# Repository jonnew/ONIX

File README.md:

# NOTE: This repository has been split into individual `onix-<project>` repos that are hosted on the [open-ephys github account](https://github.com/open-ephys). This repo has been archived.

[ONIX](https://open-ephys.github.io/onix-docs/index.html) is a collection
of [ONI](https://github.com/jonnew/ONI)-compatible hardware and API
for serialized, very-high channel count, closed-loop electrophysiology. It is
an evolution of the first-generation hardware and software introduced in [Open
Ephys project](http://www.open-ephys.org/) and involves many of the same
developers.  The firmware and API are general purpose -- they can be used to
acquire from and control custom headstages with arbitrary arrangements of
sensors and actuators (e.g. cameras, bioamplifier chips, LED drivers, etc.) and
are not limited to the hardware in this repository.

__Documentation__ : https://open-ephys.github.io/onix-docs/index.html

__Citing this work__: 

1. Citing the paper

  - TODO

2. Citing the repository itself

  - 

## Features
- Follows the [ONI](https://github.com/jonnew/ONI)-specification for serialization protocols, host communication
  protocols, device drivers, and host API
- Firmware and API permit acquisition and control of arbitrary arrangements of
  sensors and actuators:

    - Headstages
    - Miniscopes
    - Photometry systems
    - Etc.

- Submillisecond round-trip communication from brain, through host PC's main
  memory, and back again.
- Headstages:

    - 64-, 128-, 256-channels of electrophysiology
    - Optogenetic stimulation
    - Electrical stimulation
    - 3D-pose measurement
    - Data, user control, and power via a tiny coaxial cable
    - Wireless communication

- Low-level API implementation
- High-level API language bindings and existing integration with [Open Ephys
  GUI](http://www.open-ephys.org/gui/) and [Bonsai](http://bonsai-rx.org/).
- Quality documentation and easy routes to purchasing assembled devices.

## Software

1. API: https://github.com/jonnew/liboni
2. Bonsai package: coming soon
3. Open Ephys GUI plugin: coming soon

## Hardware

### [eib-64](eib-64/README.md)
64 Channel electrode interface board. Designed for small rodent tetrode
electrophysiology. Works with [headstage-64](./headstage-64/README.md).

### [eib-128](eib-128/README.md)
128 Channel electrode interface board. Designed for large rodent tetrode
electrophysiology. Works with [headstage-256](./headstage-256/README.md).

### [eib-256](eib-256/README.md)
256 Channel electrode interface board. Designed for large rodent tetrode
electrophysiology. Works with [headstage-256](./headstage-256/README.md).

### [headstage-64](headstage-64/README.md)
Serialized, multifunction headstage for small rodents. Supports 64 channels.
Designed to interface with [eib-64](./eib-64/README.md).

### [headstage-256](headstage-256/README.md)
Serialized, multifunction headstage for large rodents. Supports both 128 or 256
channels. Designed to interface with [eib-128](./eib-128/README.md) or
[eib-256](./eib-256/README.md)

### [fmc-host](fmc-host/README.md)
Base board for facilitating PCIe communication, via FMC compatiable and
PCIe-capable FPGA based board (e.g. [Numato Lab
Nereid](https://numato.com/product/nereid-kintex-7-pci-express-fpga-development-board).
This board plugs into the FMC connector on the base board. It provides
communication with one headstage and lots of other analog and digital IO.

### [analog-io-breakout](analog-io-breakout/README.md)
Passive breakout board for acquiring and generating analog signals through BNC,
SMA, ribbon, or straight wire connections. Plugs into fmc-host using a 26-pin
shrunk delta ribbon cable.

### [nanoz-adapter-64](./nanoz-adapter-64/README.md)
Adapter to interface eib-64 with the popular
[nanoZ](http://www.white-matter.com/nanoz/) electrode impedance tester and
plating device.

### [nanoz-adapter-128-256](./nanoz-adapter-128-256/README.md)
Multiplexed adapter to interface eib-128 and eib-256 with the popular
[nanoZ](http://www.white-matter.com/nanoz/) electrode impedance tester and
plating device.

### [test-board-64](./test-board-64)
Test board for headstage-64. Allows injecting simulated biopotentials into
headstage modules via a selectable passive attenuator. Provides LEDs and
simulated electrical loads for optical and electrical stimulation.

### [test-board-128-256](./test-board-128-256)
Test board for headstage, and headstage-256 modules. Allows injecting simulated
biopotentials into headstage modules via a selectable passive attenuator.
Provides LEDs and simulated electrical loads for optical and electrical
stimulation.

### [headstage-programmer](headstage-programmer/README.md)
JTAG breakout for the [Intel USB Blaster 2](https://www.digikey.com/short/qqw7hm)
used to program the headstages' MAX10 FPGA.

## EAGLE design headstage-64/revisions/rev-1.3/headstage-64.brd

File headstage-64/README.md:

:warning: This project has moved to a dedicated repository: https://github.com/open-ephys/onix-headstage-64
This folder should be considered archived.

# headstage-64
Serialized, multifunction headstage for small rodents. Designed to function
with [eib-64](../eib-64/README.md).

## Electrophysiology
This heastage uses an [Intan RHD2164]() bioamplifier chip. This chip provides:
- 64 channels of ephys are pinned out through the large mezzanine connector on the
  bottom of the headstage
- 3 auxiliary channels
    - AUX 1 and 2 are pinned out on the bottom of the headstage to an unpopulated
      mezzanine connector
    - Channel 3 is tied to the electrical stimulator's current measurement circuit

## 3D Position Tracking
Headstage-64 featurs 4 TS4231 Vive lighthouse receivers for 3D position
tracking. They work with V2 lighthouses. To set up tracking,

1. Serial into each of the basestations using the USB connection on the back
   and set up a terminal conneciton using `screen /dev/ttyACM0 115200` or
   similar

2. Once connected you can hit Tab to see commands

3. Set the mode of one base staiton to 1 (mode 1) and the other to 2 (mode 2).

## 3D Orientation Tracking
TODO

## Neural Stimulators
Headstage-64 provides onboard electrical and optical stimulation. Stimulus
trains can be parameterized in a similar way to the master-8 or pulse pal.
Electical and optical stimulus trains cannot be delivered simultaneously.
If there is a conflict, electical stimuluation will take priority and optical
stimulus triggers will be ignored.

To acheive the shortest latency, electrical and optical stimulation can be triggered
using the GPIO1 serializer output. Because both stimulators share this trigger line,
it is important to only enable one of the devices (using its ENABLE register) prioir
to toggling this pin.

### Optical Stimulation

Q. Can i parallel the Cathode connections to increase max current
A. Yes.

### Electical Stimulation
The electrical stimulation cicuit is an improved Howland current pump followed by
an precision current measurement circuit. The current pump is supplied by +/-15V
rails and can supply up to +/- 2.5 mA. The output c

ISTIM = (VDAC  - 2.5)/1000.
e.g.
VDAC = 2.5   -> ISTIM = 0
VDAC = 5.0   -> ISTIM = 2.5 mA
VDAC = 0.0   -> ISTIM = -2.5mA

and

Imeas = 400 * ISTIM + 1.25V
e.g.
ISTIM = 0      -> IMEAS = 1.25V
ISTIM = 2.5mA  -> IMEAS = 2.25V
ISTIM = -2.5mA -> IMEAS = 0.25V

## Schematic

## Gerber Files
{% include gerber_layers.md %}

## Bill of Materials
The BOM is located on [this google
sheet](https://docs.google.com/spreadsheets/d/1F-KWcdvH_63iXjZf0cgCfDiFX6XXW3qw6rlR8DZrFpQ/edit#gid=138167638).

## FPGA Pinout
The FPGA pinout is located on [this google
sheet](https://docs.google.com/spreadsheets/d/1oJoQ89dJNL9LIiTrRnwJ_9KGiLzJ53Tju5Lfchuvsb0/edit#gid=2100166621).

## Connector Pinout
The headstage connector pinout (ADC input mapping, stimulation connections,
etc) is located on [this google
sheet](https://docs.google.com/spreadsheets/d/11wRDYOqHN5lPb03yUdfXfK0zvaDYsVetplaNK-R90Gg/edit#gid=663991061)

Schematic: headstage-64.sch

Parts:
C1: 0.1uF; 0201T; PARTNP CL03A104KA3NNNC
C2, C3, C5, C6, C18, C27, C32, C33, C35: 0.1uF; 0201T; PARTNO C0603X5R1C104K030BC
C4, C8, C9: 0.1uF; 0201T; PARTNO CL03A104KA3NNNC
C7: 4.7uF; 0402T; PARTNO CL05A475MO5NUNC
C10, C14, C15, C21, C22, C45, C51, C59, C66, C71: 10nF; 0201T
C11, C13, C16, C20, C23, C30, C31, C48: 0.1uF; 0201T
C12, C17: 4.7uF; 0402T; PARTNO GRM155R61A475MEAAD
C19, C28, C34, C36, C49: 1uF; 0201T; PARTNO CL03A105MP3ZSNH
C24: 22uF; 0402T; PARTNO CL05A226MQ5QUNC
C25: 0.1uF; 0201T; PARTNO C1005X7R1H104K050BB
C26: 47nF; 0201T; PARTNO C1005X7R1H473K050BB
C29: 10nF; 0201T; PARTNO GRM033R71E103KE14D
C37, C39, C41, C55, C69: 10uF; 0402T; PARTNO CL05A105KO5NNNC
C38, C40, C54, C56: 10uF; 0402T; PARTNO CL05A106MQ5NUNC
C42, C64: 0.22uF; 0402T; PARTNO UMK105BJ224KV-F
C43: 2.2nF; 0201T
C44, C50, C58, C65: 4.7nF; 0201T
C46, C52, C60, C67: 22nF; 0201T
C47, C61: 47nF; 0201T
C53, C62, C68: 0.47uF; 0201T; PARTNO GRM033R60J474KE90D
C57: 10pF; 0201T
C63, C72: 1uF; 0402T; PARTNO CL05A105KO5NNNC
C70: 4.7uF; 0402T; PARTNO CL05A105KO5NNNC
C73: 22uF; 0402T; PARTNO CL05A226MQ6ZUN8
D1, D2, D3: SESD0402X1UN-0020-090; 0402T-DFN
D4, D5, D6, D8: VEMD1160X01; 0805PT
D7: XZVGR155W; LED-0201T
D9: VSKY05401006; CLP1006-2L
J1, J3, J6: COAX_XFL; X_FL_R_SMT_1(02)
J2, J4, J7: PINHD-1X4HEADSTAGE64-DAUGHTER-CARD-CASTELLATED; HEADSTAGE64-DAUGHER-CARD-CASTELLATED
J5: PINHD-1X4HEADSTAGE64_DAUGHTER-CARD; HEADSTAGE-64-DAUGHTER-CARD
J8: DF40C-70DP-0.4V(51); DF40-70HEAD-LESS-SILK
J9: PINHD-1X5_HALF_CONNETOR; DF40-10HEAD_HALF
L1, L3, L5: CIG21L4R7MNE; 0805T
L2: BLM18KG601SN1D; 0603T
L4: CBC3225T101MR; 1210T
L6, L7, L8, L10: BLM15PX601SN1D; 0402T; PARTNO BLM15PX601SN1D
L9, L11: MLZ2012M100WT000; 0805T
L12: LQM21PN1R0NGRD; 0805T
R1: 9k, 0.1%; 0201T
R2: 1k, 0.1%; 0201T
R3, R9, R10, R20, R21, R43: 1k; 0201T
R4, R5, R6, R7, R8, R11, R14, R16, R17, R18, R19: 10k, 0.1%; 0201T
R12, R31, R34, R35, R47: 100; 0201T
R13: 2.86k; 0201T
R15: 590; 0201T
R22, R23, R27, R28, R32, R33, R38, R39, R40, R49, R53, R54, R55, R56, R57: 10k; 0201T
R24, R26, R36, R42: 15k; 0201T
R25: 49.9; 0201T
R29: 0; 0201T
R30: 100k; 0201T
R37: 2k; 0201T
R41, R44, R51, R52: 4.7k; 0201T
R45, R50: 1M; 0201T
R46: 90.9k; 0201T
R48: 83.3k; 0201T
TP1, TP2, TP5, TP6: VCC; TP07R
TP3, TP4: TPTP09R; TP09R
TP7, TP8, TP9, TP10, TP11, TP12, TP13: TPTP06R; TP06R
TP14: gnd; TP06R
TP15: VCC; TP06R
U1: ADA4062-4ACPZ-R7; CP_16_27-L
U2: AD5681RBCPZ-1RL7; CP_8_10-L
U3: CAT4016_QFN; QFN24-4X4; PARTNO CAT4016HV6-GT2
U4: TPL0501_UQFN; UQFN; PARTNO TPL0501-100RSER
U5: DG509B; MQFN16-1.8X2.6
U6, U8, U11, U12: TS4231; WLCSP3X3
U7: RHD2064_BGA; BGA104_0.5MM
U9: DS90UB913A_WQFN; WQFN32-5X5
U10: BNO055; LGA-28-3.8X5.2
U13, U15: TLV70733; X2SON
U14: 10M08DC; VBGA81-4X4
U16: LT3463; DFN103X3
U17: TLV70725; X2SON
U18: TPS62621; XBGA6_1.2X0.8
U19: ASCO-50.000MHZ-EK-T3; ASCO
U20: TLV70712; X2SON

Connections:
!IMU_BL: R28.2, U10.4 (!BOOT_LOAD)
!IMU_RESET: R32.1, U10.11 (!RESET)
$N324: C50.1, C51.1, C52.1, C53.1, C54.1, L10.2, U14.A8 (VCCD_PLL2)
+1V2: C43.1, C44.1, C45.1, C46.1, C47.1, C48.1, C49.1, C73.1, L10.1, U14.B2 (VCC), U14.B9 (VCC), U14.H2 (VCC), U14.H8 (VCC), U20.1 (OUT)
+1V8: C13.1, C14.1, C15.1, C16.1, C17.1, C70.1, L6.1, L8.1, L12.1, R27.1, U9.11 (VDDT), U9.28 (VDDD), U18.C1 (FB)
+2V5: C56.1, C65.1, C66.1, C67.1, C68.1, C72.1, U14.B1 (VCCA3), U14.B8 (VCCA2), U14.J1 (VCCA1), U14.J9 (VCCA4), U17.1 (OUT), U20.3 (EN), U20.4 (IN)
+3V3: C3.1, C5.1, C18.1, C20.1, C21.1, C27.1, C31.1, C32.1, C35.1, C40.1, C58.1, C59.1, C60.1, C61.1, C62.1, C71.1, R22.1, R28.1, R32.2, R33.1, R37.1, R38.1, R39.1, R40.1, R41.2, R44.1, R51.2, R52.1, R53.1, R54.1, R55.1, R56.1, TP14.TP, U2.2 (VLOGIC), U4.7 (VDD), U6.C3 (DVDD), U8.C3 (DVDD), U9.25 (VDDIO), U10.3 (VDD), U10.28 (VDDIO), U11.C3 (DVDD), U12.C3 (DVDD), U14.D5 (VCCIO8), U14.E4 (VCCIO1_2), U14.E6 (VCCIO5_6), U14.F5 (VCCIO3), U15.1 (OUT), U19.1 (EN), U19.4 (VCC)
+3V3_AN: C30.2, C38.1, J9.4 (5), U7.M15 (VDD), U7.M16 (LVDS_EN), U7.N2 (VDD), U7.N15 (VDD), U13.1 (OUT)
+15V0: C1.1, C8.1, C42.1, R45.2, U1.3 (V+), U5.12 (V+), U16.1 (VOUT1)
-15V0: C4.1, C9.1, C57.2, C64.1, D9.A, R50.1, U1.10 (V-), U1.PAD (V-), U5.1 (V-)
AGND: C29.2, C30.1, C37.2, C38.2, J8.70, J8.M1, J8.M2, J8.M4, J9.M1 (1), J9.M2 (6), L7.2, R29.1, TP1.TP, U7.M2 (VESD), U7.M17 (GND), U7.N1 (GND), U7.N6 (GND), U13.2 (GND), U13.PAD (GND)
AUXIN2: J9.2 (3), TP6.TP, U7.N4 (AUXIN2)
AUXIN3: J9.1 (2), TP5.TP, U7.N3 (AUXIN1)
CONFIG_SEL: R57.1, U14.C6 (CONFIG_SEL/C6)
CONF_DONE: R56.2, U14.A2 (DIFFIO_RX_T24N/CONF_DONE/A2)
DAC_CS: U2.5 (!SYNC), U14.A5 (DIFFIO_RX_T18N/A5)
DATA1: U6.C1 (D/CFGDATA), U14.C7 (DIFFIO_RX_R33P/PLL_R_CLKOUTP/C7)
DATA2: U8.C1 (D/CFGDATA), U14.C3 (DIFFIO_RX_T26N/C3)
DATA3: U11.C1 (D/CFGDATA), U14.A7 (DIFFIO_RX_T16P/A7)
DATA4: U12.C1 (D/CFGDATA), U14.B6 (DIFFIO_RX_T16N/DEV_CLRN/B6)
DIN0: U9.19 (DIN0), U14.J6 (DIFFIO_TX_RX_B12P/J6)
DIN1: U9.20 (DIN1), U14.G6 (DIFFIO_TX_RX_B14N/G6)
DIN2: U9.21 (DIN2), U14.H7 (DIFFIO_TX_RX_B14P/H7)
DIN3: U9.22 (DIN3), U14.J7 (DIFFIO_TX_RX_B16N/J7)
DIN4: U9.23 (DIN4), U14.G8 (DIFFIO_RX_R7P/G8)
DIN5: U9.24 (DIN5), U14.G9 (DIFFIO_RX_R7N/G9)
DIN6: U9.26 (DIN6), U14.F7 (DIFFIO_RX_R1N/F7)
DIN7: U9.27 (DIN7), U14.E7 (DIFFIO_RX_R14N/CLK2N/E7)
DIN8: U9.29 (DIN8), U14.E8 (DIFFIO_RX_R14P/CLK2P/E8)
DIN9: U9.30 (DIN9), U14.C8 (DIFFIO_RX_R27P/C8)
DIN10: U9.31 (DIN10), U14.C5 (CRC_ERROR/C5)
DIN11: U9.32 (DIN11), U14.C4 (DIFFIO_RX_T26P/C4)
E0: J8.2, U7.K2 (IN0)
E1: J8.68, U7.J1 (IN1)
E2: J8.3, U7.J2 (IN2)
E3: J8.67, U7.H1 (IN3)
E4: J8.4, U7.H2 (IN4)
E5: J8.66, U7.G1 (IN5)
E6: J8.5, U7.G2 (IN6)
E7: J8.65, U7.F1 (IN7)
E8: J8.6, U7.F2 (IN8)
E9: J8.64, U7.E1 (IN9)
E10: J8.7, U7.E2 (IN10)
E11: J8.63, U7.D1 (IN11)
E12: J8.8, U7.D2 (IN12)
E13: J8.62, U7.C1 (IN13)
E14: J8.9, U7.C2 (IN14)
E15: J8.61, U7.B1 (IN15)
E16: J8.10, U7.A1 (IN16)
E17: J8.60, U7.B2 (IN17)
E18: J8.11, U7.A2 (IN18)
E19: J8.59, U7.B3 (IN19)
E20: J8.12, U7.A3 (IN20)
E21: J8.58, U7.B4 (IN21)
E22: J8.13, U7.A4 (IN22)
E23: J8.57, U7.B5 (IN23)
E24: J8.14, U7.A5 (IN24)
E25: J8.56, U7.B6 (IN25)
E26: J8.15, U7.A6 (IN26)
E27: J8.55, U7.B7 (IN27)
E28: J8.16, U7.A7 (IN28)
E29: J8.54, U7.B8 (IN29)
E30: J8.17, U7.A8 (IN30)
E31: J8.53, U7.B9 (IN31)
E32: J8.18, U7.A9 (IN32)
E33: J8.52, U7.A10 (IN33)
E34: J8.19, U7.B10 (IN34)
E35: J8.51, U7.A11 (IN35)
E36: J8.20, U7.B11 (IN36)
E37: J8.50, U7.A12 (IN37)
E38: J8.21, U7.B12 (IN38)
E39: J8.49, U7.A13 (IN39)
E40: J8.22, U7.B13 (IN40)
E41: J8.48, U7.A14 (IN41)
E42: J8.23, U7.B14 (IN42)
E43: J8.47, U7.A15 (IN43)
E44: J8.24, U7.B15 (IN44)
E45: J8.46, U7.A16 (IN45)
E46: J8.25, U7.B16 (IN46)
E47: J8.45, U7.A17 (IN47)
E48: J8.26, U7.B17 (IN48)
E49: J8.44, U7.C16 (IN49)
E50: J8.27, U7.C17 (IN50)
E51: J8.43, U7.D16 (IN51)
E52: J8.28, U7.D17 (IN52)
E53: J8.42, U7.E16 (IN53)
E54: J8.29, U7.E17 (IN54)
E55: J8.41, U7.F16 (IN55)
E56: J8.30, U7.F17 (IN56)
E57: J8.40, U7.G16 (IN57)
E58: J8.31, U7.G17 (IN58)
E59: J8.39, U7.H16 (IN59)
E60: J8.32, U7.H17 (IN60)
E61: J8.38, U7.J16 (IN61)
E62: J8.33, U7.J17 (IN62)
E63: J8.37, U7.K16 (IN63)
ENV1: U6.C2 (E/CFGCLK), U14.B5 (DIFFIO_RX_T19N/B5)
ENV2: U8.C2 (E/CFGCLK), U14.C2 (DIFFIO_RX_L1N/C2)
ENV3: U11.C2 (E/CFGCLK), U14.D9 (DIFFIO_RX_R16N/CLK3N/D9)
ENV4: U12.C2 (E/CFGCLK), U14.B7 (DIFFIO_RX_R33N/PLL_R_CLKOUTN/B7)
ESTIM_POW_EN: R49.1, U14.A6 (DIFFIO_RX_T18P/DEV_OEA6), U16.8 (!SHDN2), U16.9 (!SHDN1)
GND: C1.2, C2.2, C3.2, C4.2, C5.2, C6.2, C7.2, C8.2, C9.2, C10.2, C11.2, C12.2, C13.2, C14.2, C15.2, C16.2, C17.2, C18.2, C19.2, C20.2, C21.2, C22.2, C23.2, C24.2, C27.2, C28.2, C31.2, C32.2, C33.1, C34.2, C35.2, C36.2, C39.2, C40.2, C41.2, C42.2, C43.2, C44.2, C45.2, C46.2, C47.2, C48.2, C49.2, C50.2, C51.2, C52.2, C53.2, C54.2, C55.2, C56.2, C58.2, C59.2, C60.2, C61.2, C62.2, C64.2, C65.2, C66.2, C67.2, C68.2, C69.2, C70.2, C71.2, C72.2, C73.2, J5.2, J5.4, L7.1, R19.1, R21.1, R23.2, R24.1, R25.1, R26.1, R30.2, R36.1, R42.1, R43.2, R46.1, R49.2, R57.2, TP3.TP, TP15.TP, U2.3 (GND), U2.PAD (GND), U3.1 (GND), U3.PAD (GND), U4.4 (GND), U4.8 (LA), U5.2 (X0), U5.13 (GND), U5.14 (B), U6.B2 (AVSS), U6.B3 (AVSS2), U8.B2 (AVSS), U8.B3 (AVSS2), U9.6 (ID), U9.7 (RES), U9.PAD (GND), U10.2 (GND), U10.5 (PS1), U10.6 (PS0), U10.15 (GNDIO), U10.16 (GNDIO), U10.17 (COM3/ADDR), U10.18 (COM2), U10.25 (GNDIO), U11.B2 (AVSS), U11.B3 (AVSS2), U12.B2 (AVSS), U12.B3 (AVSS2), U14.A1 (GND), U14.A9 (GND), U14.B4 (GND), U14.D1 (GND), U14.D7 (GND), U14.E5 (GND), U14.E9 (GND), U14.F4 (GND), U14.F6 (GND), U14.H1 (GND), U14.H5 (GND), U14.H9 (GND), U15.2 (GND), U15.PAD (GND), U16.PAD (GND), U17.2 (GND), U17.PAD (GND), U18.C2 (GND), U19.2 (GND), U20.2 (GND), U20.PAD (GND)
GND1: D2.A, J3.P$2 (2), J3.P$3 (2), J3.P$4 (2), J4.2, J4.4
GND2: D1.A, J1.P$2 (2), J1.P$3 (2), J1.P$4 (2), J2.2, J2.4
GND3: D3.A, J6.P$2 (2), J6.P$3 (2), J6.P$4 (2), J7.2, J7.4
GPIO0: J9.3 (4), TP4.TP, U9.15 (GPIO0), U14.A3
GPIO1: U9.16 (GPIO1), U14.H6 (DIFFIO_TX_RX_B12N/H6)
HSYNC: U9.1 (HSYNC), U14.F2 (DIFFIO_RX_L18P/CLK0P/F2)
IMU_INT: U10.14 (INT)
IMU_SCL: R41.1, U10.19 (COM1/SCL/RX), U14.E3
IMU_SDA: R51.1, U10.20 (COM0/SDA/TX), U14.F9 (DIFFIO_RX_R10N/F9)
ISTIM: J8.1, U5.6 (X), U5.10 (Y1)
ISTIM_MONO: R14.1, R19.2, U7.N5 (AUXIN3)
ISTIM_PRE: R12.1, U1.9 (+IN), U5.7 (Y)
JTAGEN: R38.2, U14.D2 (JTAGEN/D2)
LED-1: J8.34, U3.5 (LED1), U3.6 (LED2), U3.7 (LED3), U3.8 (LED4), U3.9 (LED5), U3.10 (LED6), U3.11 (LED7), U3.12 (LED8)
LED-2: J8.35, U3.13 (LED9), U3.14 (LED10), U3.15 (LED11), U3.16 (LED12), U3.17 (LED13), U3.18 (LED14), U3.19 (LED15), U3.20 (LED16)
LED_BLANK: R53.2, U3.21 (BLANK), U14.C9 (DIFFIO_RX_R27N/C9)
LED_LATCH: U3.4 (LATCH), U14.J8 (DIFFIO_TX_RX_B16P/J8)
MIDFILT: J5.1, L4.1, R10.1
MOSI: U2.6 (DIN), U3.2 (SIN), U4.2 (DIN), U14.A4 (DIFFIO_RX_T19P/A4)
unnamed: R15.2, U4.6 (WA)
unnamed: C63.1, L11.1, U16.4 (SW2)
unnamed: C57.1, R48.1, R50.2, U16.6 (FB2)
unnamed: D4.C, U6.A3 (IIN-)
unnamed: D4.A, U6.A2 (IIN+)
unnamed: R24.2, U6.B1 (RBIAS)
unnamed: C19.1, U6.A1 (AVDD)
unnamed: L9.1, U16.2 (SW1)
unnamed: D5.C, U8.A3 (IIN-)
unnamed: D5.A, U8.A2 (IIN+)
unnamed: R26.2, U8.B1 (RBIAS)
unnamed: C28.1, U8.A1 (AVDD)
unnamed: C6.1, C7.1, L2.1, L4.2, R10.2
unnamed: R15.1, U3.23 (RSET)
unnamed: D6.C, U11.A3 (IIN-)
unnamed: D6.A, U11.A2 (IIN+)
unnamed: R36.2, U11.B1 (RBIAS)
unnamed: C34.1, U11.A1 (AVDD)
unnamed: C63.2, D9.C, U16.5 (D2)
unnamed: R1.2, R2.2, R12.2, U1.4 (+IN)
unnamed: R21.2, U5.11 (Y0)
unnamed: R45.1, R46.2, U16.10 (FB1)
unnamed: J4.1, L3.2, R9.2
unnamed: D8.C, TP7.TP, U12.A3 (IIN-)
unnamed: R48.2, U16.7 (VREF)
unnamed: C25.2, U9.13 (DOUT+)
unnamed: D7.2 (A), R37.2
unnamed: R33.2, U9.9 (PDB)
unnamed: C26.2, U9.12 (DOUT-)
unnamed: C26.1, R25.2
unnamed: R27.2, R30.1, U9.8 (MODE)
unnamed: C10.1, C11.1, C12.1, L6.2, U9.10 (VDDPLL)
unnamed: C22.1, C23.1, C24.1, L8.2, U9.14 (VDDCML)
unnamed: C29.1, U7.N17 (ADC_REF)
unnamed: U14.D8 (DIFFIO_RX_R16P/CLK3P/D8), U19.3 (OUT)
unnamed: D8.A, TP8.TP, U12.A2 (IIN+)
unnamed: TP2.TP, U7.N16 (AUXOUT)
unnamed: R42.2, U12.B1 (RBIAS)
unnamed: C36.1, U12.A1 (AVDD)
unnamed: R22.2, U5.16 (EN)
unnamed: R54.2, U14.D6 (NCONFIG/D6)
unnamed: L12.2, U18.B1 (SW)
unnamed: J2.1, L1.2, R3.2
unnamed: J7.1, L5.2, R20.2
unnamed: R1.1, R4.2, U1.2 (+IN)
unnamed: R5.2, R11.1, U1.1 (-IN)
unnamed: R2.1, R11.2, U1.15 (OUT)
unnamed: R16.1, R17.2, U1.6 (OUT)
unnamed: R13.1, R16.2, U1.5 (-IN)
unnamed: R8.1, R13.2, U1.8 (-IN)
unnamed: R6.2, R8.2, U1.7 (OUT)
unnamed: R7.1, R14.2, U1.14 (OUT)
unnamed: R6.1, R7.2, U1.12 (-IN)
unnamed: R17.1, R18.2, U1.11 (+IN)
unnamed: C33.2, U10.9 (CAP)
NSTATUS: R55.2, U14.B3 (DIFFIO_RX_T24P/NSTATUS/B3)
PCLK: U9.3 (PCLK1), U14.G2 (DIFFIO_RX_L20N/CLK1N/G2)
POT_CS: U4.3 (!CS), U14.G7 (DIFFIO_RX_R1P/G7)
REF: J8.69, R29.2, U7.M1 (REF_ELEC)
RHD_CLK_N: R34.1, U7.N9 (SCLK-), U14.G5 (DIFFIO_TX_RX_B3P/G5)
RHD_CLK_P: R34.2, U7.N10 (SCLK+), U14.G4 (DIFFIO_TX_RX_B3N/G4)
RHD_CS_N: R31.1, U7.N7 (!CS!-), U14.J2 (DIFFIO_TX_RX_B1P/J2)
RHD_CS_P: R31.2, U7.N8 (!CS!+), U14.H3 (DIFFIO_TX_RX_B1N/H3)
RHD_MISO_N: R47.1, U7.N13 (MISO-), U14.J5 (DIFFIO_TX_RX_B9P/J5)
RHD_MISO_P: R47.2, U7.N14 (MISO+), U14.J4 (DIFFIO_TX_RX_B9N/J4)
RHD_MOSI_N: R35.1, U7.N11 (MOSI-), U14.H4 (DIFFIO_TX_RX_B5P/H4)
RHD_MOSI_P: R35.2, U7.N12 (MOSI+), U14.J3 (DIFFIO_TX_RX_B5N/J3)
SCL: R44.2, U9.4 (SCL), U14.G3 (DIFFIO_RX_L27P/G3)
SCLK: U2.4 (SCLK), U3.3 (CLK), U4.5 (SCLK), U14.F3 (DIFFIO_RX_L27N/F3)
SDA: R52.2, U9.5 (SDA), U14.F8 (DIFFIO_RX_R10P/F8)
SIGOUT: C25.1, J5.3
STATUS: D7.1 (C), U14.C1 (DIFFIO_RX_L1P/C1)
STIM_NULL: R23.1, U5.15 (A), U14.F1 (DIFFIO_RX_L18N/CLK0N/F1)
TCK: R43.1, TP11.TP, U14.D4 (DIFFIO_RX_L11P/TCK/D4)
TDI: R40.2, TP12.TP, U14.E1 (DIFFIO_RX_L12N/TDI/E1)
TDO: TP13.TP, U14.E2 (DIFFIO_RX_L12P/TDO/E2)
TMS: R39.2, TP10.TP, U14.D3 (DIFFIO_RX_L11N/TMS/D3)
VCOAX: C2.1, C37.1, C39.1, C41.1, C55.1, C69.1, J8.36, J8.M3, L2.2, L9.2, L11.2, TP9.TP, U2.1 (AVDD), U3.24 (VDD), U13.3 (EN), U13.4 (IN), U15.3 (EN), U15.4 (IN), U16.3 (VIN), U17.3 (EN), U17.4 (IN), U18.A1 (MODE), U18.A2 (VIN), U18.B2 (EN)
VDAC: R4.1, U2.8 (VOUT)
VREF_2V5: R5.1, R18.1, U2.7 (VREF)
VSYNC: U9.2 (VSYNC), U14.G1 (DIFFIO_RX_L20P/CLK1P/G1)
_SIGOUT: D2.C, J3.P$1 (1), J4.3, L3.1, R9.1
_SIGOUT1: D1.C, J1.P$1 (1), J2.3, L1.1, R3.1
_SIGOUT2: D3.C, J6.P$1 (1), J7.3, L5.1, R20.1

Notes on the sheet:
NB: Inductors pass 250mA DC max before they are used to generate a flyback voltage. Because we are dealing with a very low current application, we can probably get away with inductors that saturate below 250 mA so long as they are capable of handling the current. The MLZ2012M100WT000 saturates at 2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
NB: VCoax must NOT exceed 5.5V
Programming interface
INPUT
ESTIM
OPTOSTIM
SERIALIZER
FPGA
ADC
TRACKING
POWER
NB: Because we are suing a 3.3V IO voltage for bank 3, the LVDS produced here is technically out of spec. The lines sit at 1.6V and swing about 600 mV. This is a result of using 3.3V supply on an FPGA that nominally requires a 2.5 rail to get LVDS to its standard 1.2V common mode voltage with 400 m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
DNP
NB: CLK3 drives PLL2
NB: IO daughter boards. Multiple allows them to be replaced if coax connector gets worn out.
NB: ISTIM = (VDAC - 2.5)/1000. e.g. VDAC = 2.5 -> ISTIM = 0 VDAC = 5.0 -> ISTIM = 2.5 mA VDAC = 0.0 -> ISTIM = -2.5mA and Imeas = 400 * ISTIM + 1.25V e.g. ISTIM = 0 -> IMEAS = 1.25V ISTIM = 2.5mA -> IMEAS = 2.25V ISTIM = -2.5mA -> IMEAS = 0.25V
I2C Selected
NB To get the best performance out of BNO055, it is recommended to use the external 32.768 kHz crystal.
NB: Decoupling relies on input caps for the LDO regulators.

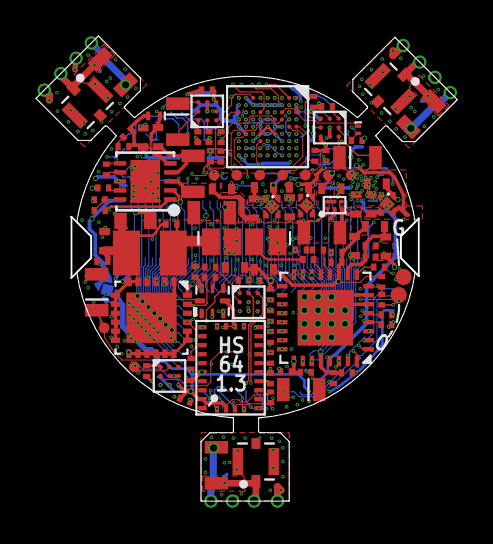
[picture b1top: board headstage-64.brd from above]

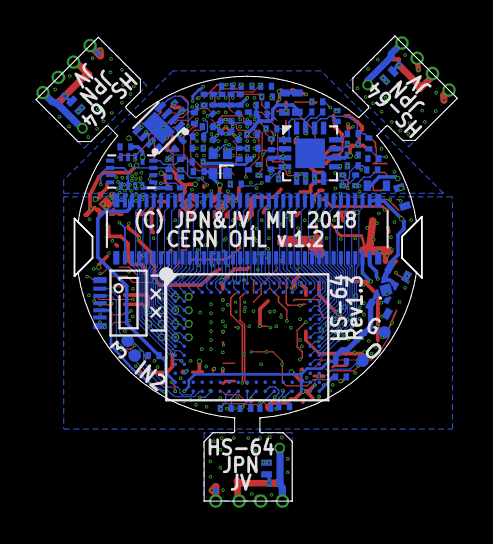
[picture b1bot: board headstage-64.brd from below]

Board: 8 copper layers, 23.4 x 25.8 mm, 195 parts (82 on the bottom side), 204 nets.

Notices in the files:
headstage-256/fpga/headstage-128-256.qsf:
Copyright (C) 2017  Intel Corporation. All rights reserved.
breakout/breakout.sch:
LICENSE: CC BY-NC-SA 4.0
breakout/revisions/rev-1.3/breakout.sch:
LICENSE: CERN OHL v1.2
fmc-host/revisions/rev-1.3/fmc-host.brd:
CERN OHL v1.2
test-board-64/revisions/rev-1.2/test-board-64.sch:
LICENSE: (c) Jon Newman CERN OHL v1.2
